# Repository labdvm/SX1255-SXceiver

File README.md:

# SX1255-SXceiver-HAT
This is modified SXceiver by shared schematic from Tatu Peltola.
SX1255 HAT for RPi4-5.
# RPi4/5 with minimum 2GB RAM, fast-write micro-sd card or upgraded with M.2 nvme drive.
# The eeprom is for HW-ID and if cannot be programmed by the procedures then you must programm with eeprom programmator. " https://github.com/tejeez/sxxcvr/blob/main/dts/README.md ".
# For Tetra-TMO Base Station this is the installing procedures, " https://github.com/MidnightBlueLabs/tetra-bluestation-docs/wiki ".
https://github.com/MidnightBlueLabs/tetra-bluestation

# The PA (TQP3M9036) can amplify up to 20dBm @ (70cm-band) 
# BlueStation Tetra TMO configurator " https://dimetra.russel053.com/ "
# Z32IT

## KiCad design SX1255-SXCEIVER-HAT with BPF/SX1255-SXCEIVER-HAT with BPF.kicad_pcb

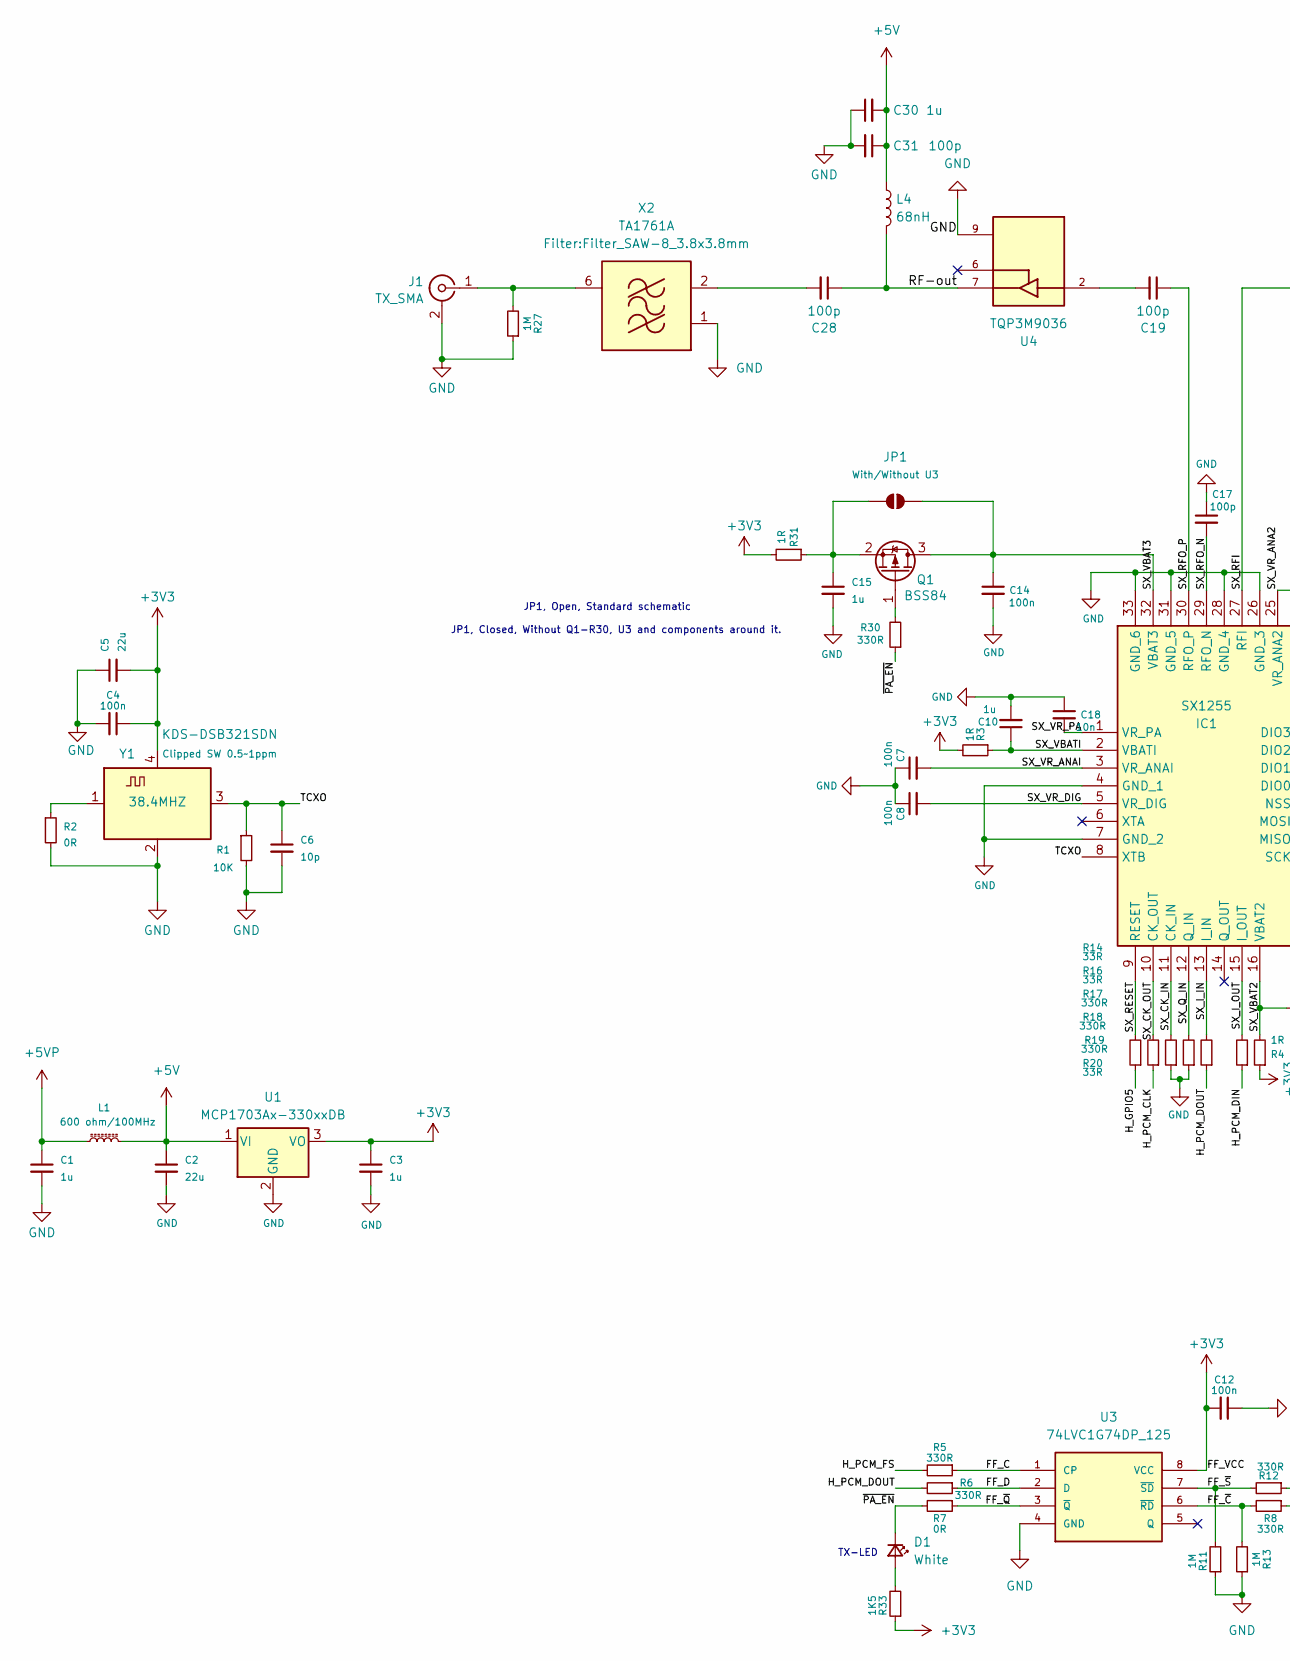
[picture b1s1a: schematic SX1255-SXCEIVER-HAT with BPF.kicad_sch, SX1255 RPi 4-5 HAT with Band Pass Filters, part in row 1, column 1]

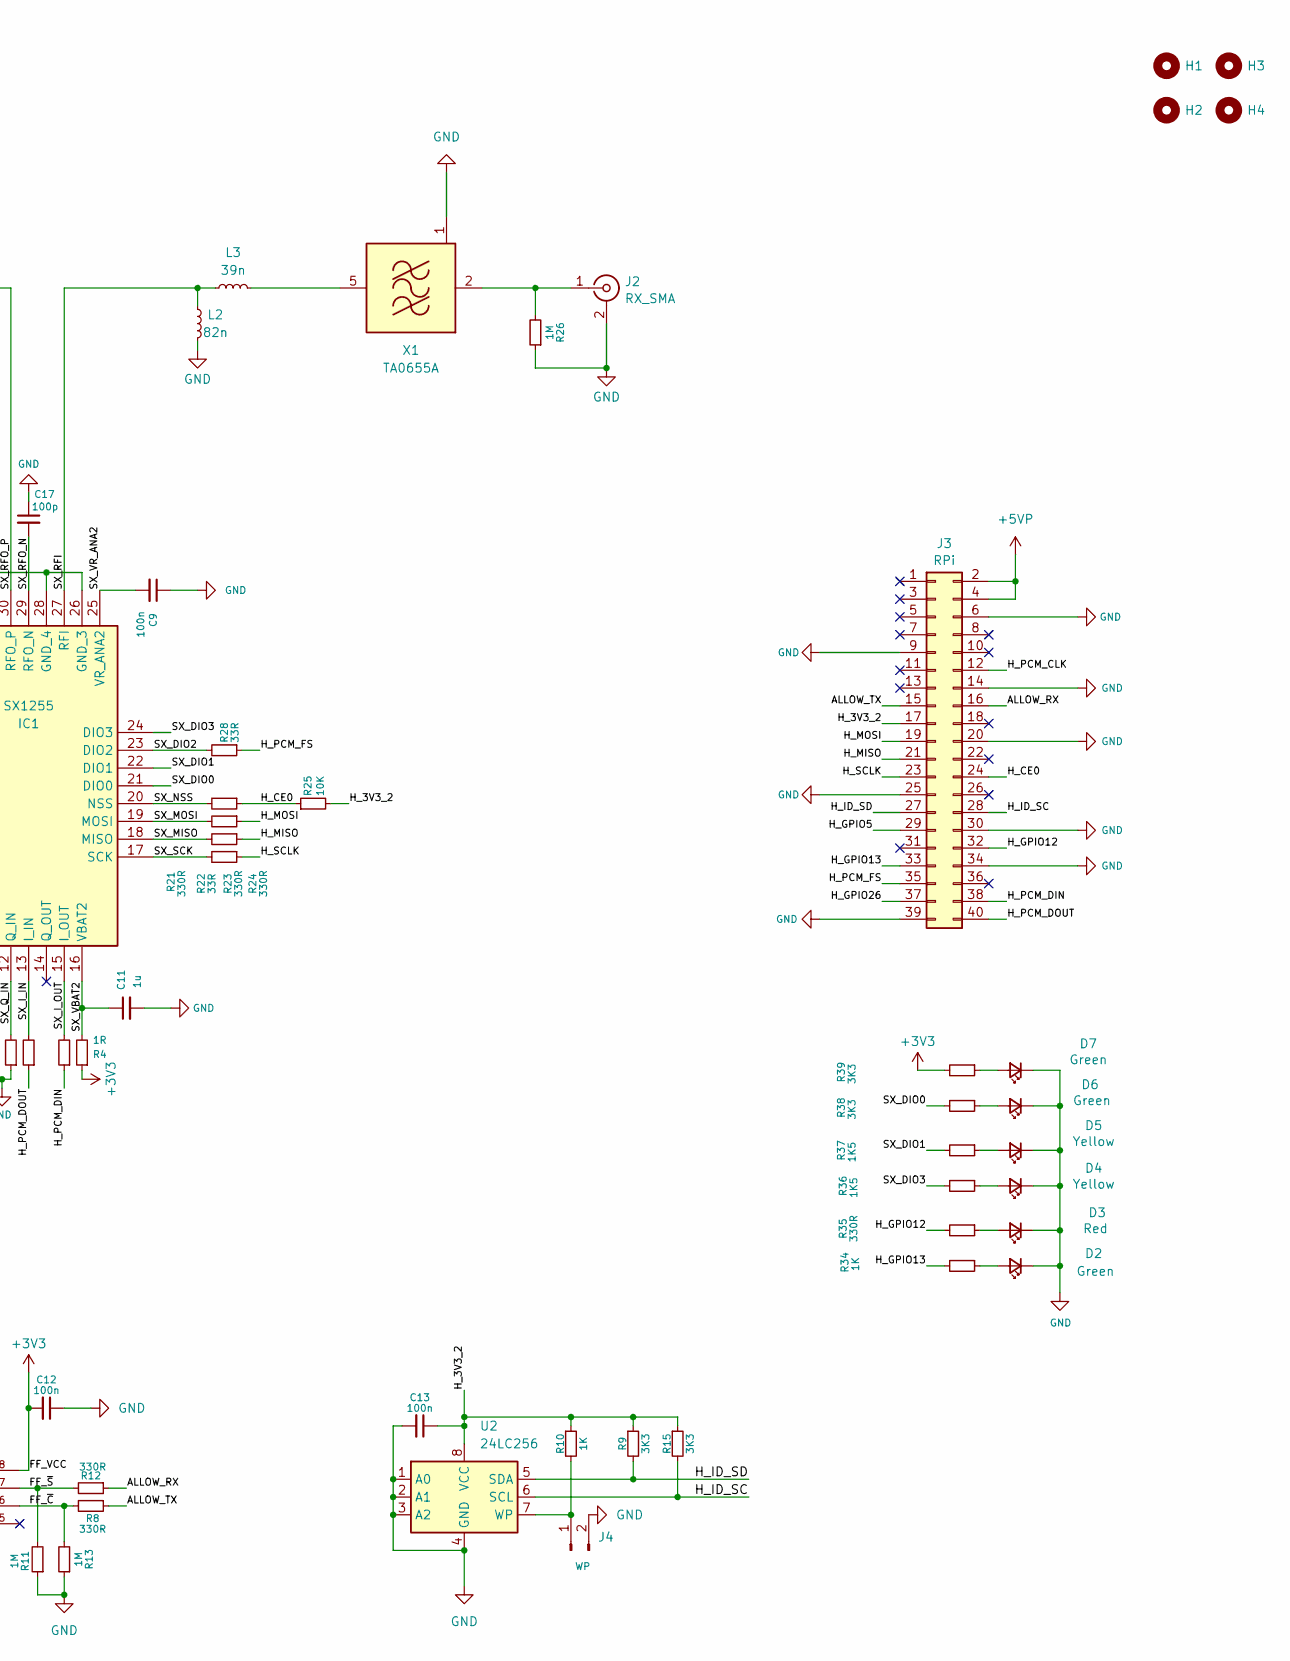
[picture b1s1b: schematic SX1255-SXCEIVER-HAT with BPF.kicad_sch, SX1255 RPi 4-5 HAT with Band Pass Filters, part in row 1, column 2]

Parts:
C1, C3, C10, C11, C15, C30: 1u; C_0603_1608Metric
C2, C5: 22u; C_1206_3216Metric
C4, C7, C8, C9, C12, C13, C14: 100n; C_0603_1608Metric
C6: 10p; C_0603_1608Metric
C17, C19, C28, C31: 100p; C_0603_1608Metric
C18: 10n; C_0603_1608Metric
D1: White; LED_0603_1608Metric_Pad1.05x0.95mm_HandSolder
D2, D6, D7: Green; LED_0603_1608Metric_Pad1.05x0.95mm_HandSolder
D3: Red; LED_0603_1608Metric_Pad1.05x0.95mm_HandSolder
D4, D5: Yellow; LED_0603_1608Metric_Pad1.05x0.95mm_HandSolder
H1, H2, H3, H4: MountingHole; MountingHole_2.7mm_M2.5_DIN965
IC1: SX1255; QFN50P500X500X80-33N-D; MPN SX1255IWLTRT
J1: TX_SMA; SMA_Amphenol_901-144_Vertical
J2: RX_SMA; SMA_Amphenol_901-144_Vertical
J3: RPi; PinSocket_2x20_P2.54mm_Vertical
J4: WP; PinHeader_1x02_P2.54mm_Vertical
JP1: With/Without U3; SolderJumper-2_P1.3mm_Open_RoundedPad1.0x1.5mm
L1: 600 ohm/100MHz; L_0805_2012Metric
L2: 82n; L_0603_1608Metric
L3: 39n; L_0603_1608Metric
L4: 68nH; C_0603_1608Metric
Q1: BSS84; SOT-23
R1, R25: 10K; R_0603_1608Metric
R2, R7: 0R; R_0603_1608Metric
R3, R4, R31: 1R; R_0603_1608Metric
R5, R6, R8, R12, R17, R18, R19, R21, R23, R24, R30, R35: 330R; R_0603_1608Metric
R9, R15, R38, R39: 3K3; R_0603_1608Metric
R10, R34: 1K; R_0603_1608Metric
R11, R13, R26, R27: 1M; R_0603_1608Metric
R14, R16, R20, R22, R28: 33R; R_0603_1608Metric
R33, R36, R37: 1K5; R_0603_1608Metric
U1: MCP1703Ax-330xxDB; SOT-223-3_TabPin2
U2: 24LC256; SOIC-8_3.9x4.9mm_P1.27mm
U3: 74LVC1G74DP_125; SOP65P400X110-8N; MOUSER_PART_NUMBER 771-LVC1GDP125
U4: TQP3M9036; SON50P200X200X95-9N; PARTREV N/A
X1: TA0655A; Filter_SAW-6_3.8x3.8mm
X2: TA1761A; Filter_SAW-8_3.8x3.8mm
Y1: 38.4MHZ; Crystal_SMD_3225-4Pin_3.2x2.5mm

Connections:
+3V3: C3.1, C4.1, C5.2, C12.2, R3.2, R4.1, R31.2, R33.1, R39.2, U1.3 (VO), U3.8 (VCC), Y1.4 (VDD)
+5V: C2.1, C30.2, C31.1, L1.2, L4.1, U1.1 (VI)
+5VP: C1.1, J3.2, J3.4, L1.1
/ALLOW_RX: J3.16, R12.1
/ALLOW_TX: J3.15, R8.1
/FF_C: R5.1, U3.1 (CP)
/FF_D: R6.1, U3.2 (D)
/FF_~C: R8.2, R13.2, U3.6 (~RD)
/FF_~Q: R7.1, U3.3 (~Q)
/FF_~S: R11.2, R12.2, U3.7 (~SD)
/H_3V3_2: C13.1, J3.17, R9.1, R10.1, R15.1, R25.2, U2.8 (VCC)
/H_CE0: J3.24, R24.1, R25.1
/H_GPIO5: J3.29, R14.1
/H_GPIO12: J3.32, R35.2
/H_GPIO13: J3.33, R34.2
/H_GPIO26: J3.37
/H_ID_SC: J3.28, R15.2, U2.6 (SCL)
/H_ID_SD: J3.27, R9.2, U2.5 (SDA)
/H_MISO: J3.21, R22.1
/H_MOSI: J3.19, R23.1
/H_PCM_CLK: J3.12, R16.1
/H_PCM_DIN: J3.38, R20.1
/H_PCM_DOUT: J3.40, R6.2, R19.1
/H_PCM_FS: J3.35, R5.2, R28.1
/H_SCLK: J3.23, R21.1
/RF-out: C28.1, L4.2, U4.7
/SX_CK_IN: IC1.11 (CK_IN), R17.2
/SX_CK_OUT: IC1.10 (CK_OUT), R16.2
/SX_DIO0: IC1.21 (DIO0), R38.2
/SX_DIO1: IC1.22 (DIO1), R37.2
/SX_DIO2: IC1.23 (DIO2), R28.2
/SX_DIO3: IC1.24 (DIO3), R36.2
/SX_I_IN: IC1.13 (I_IN), R19.2
/SX_I_OUT: IC1.15 (I_OUT), R20.2
/SX_MISO: IC1.18 (MISO), R22.2
/SX_MOSI: IC1.19 (MOSI), R23.2
/SX_NSS: IC1.20 (NSS), R24.2
/SX_Q_IN: IC1.12 (Q_IN), R18.2
/SX_RESET: IC1.9 (RESET), R14.2
/SX_RFI: IC1.27 (RFI), L2.2, L3.2
/SX_RFO_N: C17.2, IC1.29 (RFO_N)
/SX_RFO_P: C19.1, IC1.30 (RFO_P)
/SX_SCK: IC1.17 (SCK), R21.2
/SX_VBAT2: C11.1, IC1.16 (VBAT2), R4.2
/SX_VBAT3: C14.1, IC1.32 (VBAT3), JP1.2 (B), Q1.3 (D)
/SX_VBATI: C10.1, IC1.2 (VBATI), R3.1
/SX_VR_ANA2: C9.2, IC1.25 (VR_ANA2)
/SX_VR_ANAI: C7.2, IC1.3 (VR_ANAI)
/SX_VR_DIG: C8.2, IC1.5 (VR_DIG)
/SX_VR_PA: C18.2, IC1.1 (VR_PA)
/TCXO: C6.1, IC1.8 (XTB), R1.1, Y1.3 (OUT)
/~PA_EN: D1.1 (K), R7.2, R30.1
GND: C1.2, C2.2, C3.2, C4.2, C5.1, C6.2, C7.1, C8.1, C9.1, C10.2, C11.2, C12.1, C13.2, C14.2, C15.2, C17.1, C18.1, C30.1, C31.2, D2.1 (K), D3.1 (K), D4.1 (K), D5.1 (K), D6.1 (K), D7.1 (K), IC1.4 (GND_1), IC1.7 (GND_2), IC1.26 (GND_3), IC1.28 (GND_4), IC1.31 (GND_5), IC1.33 (GND_6), J1.2 (Ext), J2.2 (Ext), J3.6, J3.9, J3.14, J3.20, J3.25, J3.30, J3.34, J3.39, J4.2, L2.1, R1.2, R2.2, R11.1, R13.1, R17.1, R18.1, R26.1, R27.1, U1.2 (GND), U2.1 (A0), U2.2 (A1), U2.3 (A2), U2.4 (GND), U3.4 (GND), U4.1, U4.3, U4.4, U4.5, U4.8, U4.9, U4.V1, U4.V2, U4.V3, X1.1 (GND), X1.3 (GND), X1.4 (GND), X1.6 (GND), X2.1 (GND), X2.3 (GND), X2.4 (GND), X2.5 (GND), X2.7 (GND), X2.8 (GND), Y1.2 (GND)
unnamed: C19.2, U4.2
unnamed: D1.2 (A), R33.2
unnamed: D2.2 (A), R34.1
unnamed: D3.2 (A), R35.1
unnamed: D4.2 (A), R36.1
unnamed: D5.2 (A), R37.1
unnamed: D6.2 (A), R38.1
unnamed: D7.2 (A), R39.1
unnamed: J1.1 (In), R27.2, X2.6 (RF_out)
unnamed: J2.1 (In), R26.2, X1.2 (IN)
unnamed: J4.1, R10.2, U2.7 (WP)
unnamed: C15.1, JP1.1 (A), Q1.2 (S), R31.1
unnamed: Q1.1 (G), R30.2
unnamed: L3.1, X1.5 (OUT)
unnamed: C28.2, X2.2 (RF_In)
unnamed: R2.1, Y1.1 (Tri-State)

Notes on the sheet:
JP1, Open, Standard schematic
TX-LED
JP1, Closed, Without Q1-R30, U3 and components around it.

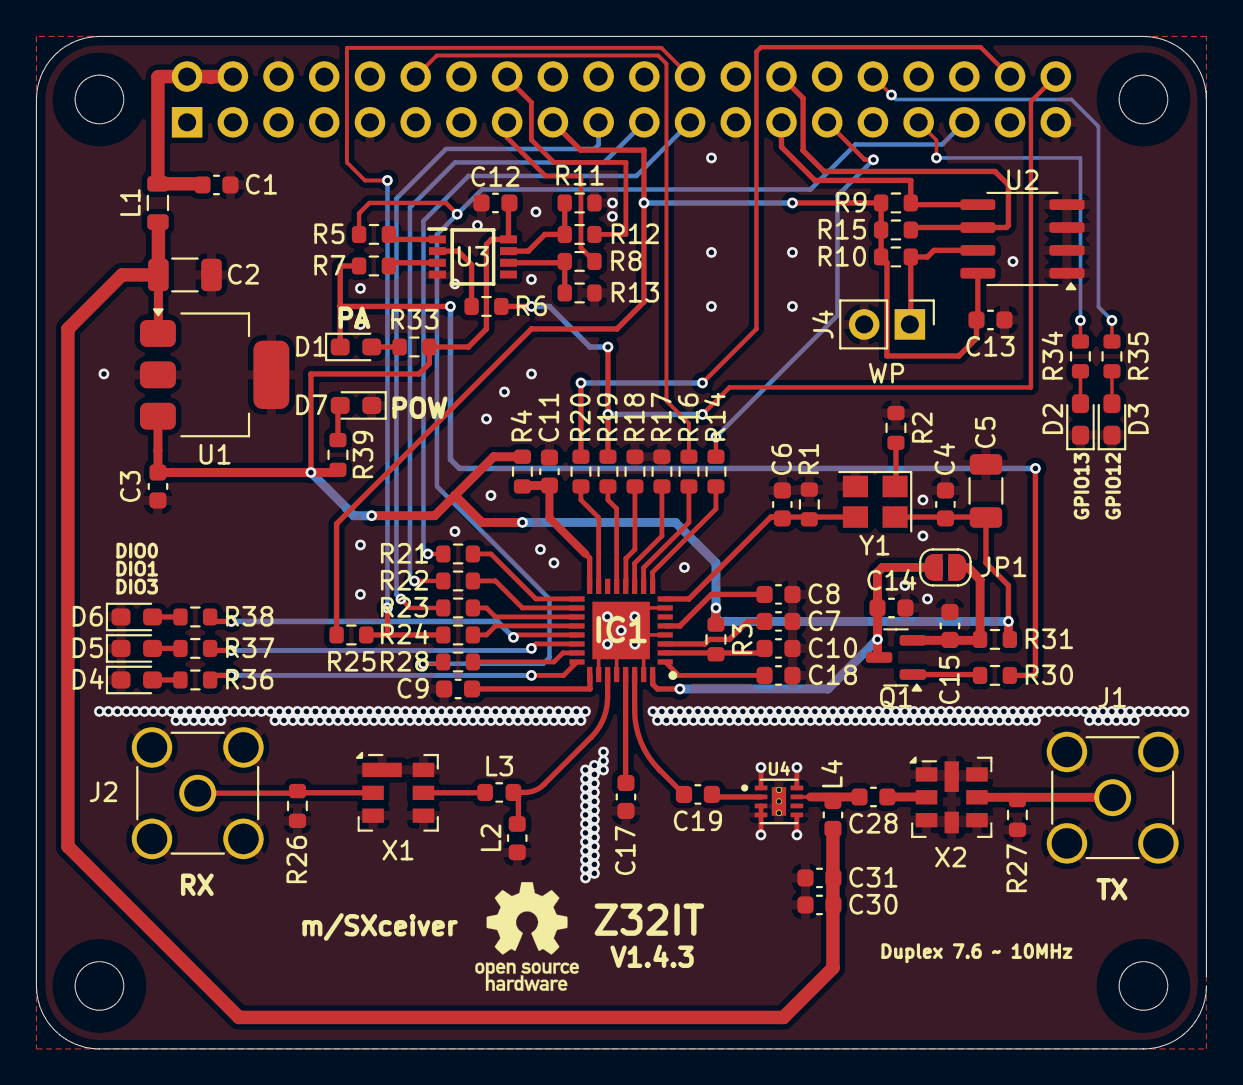
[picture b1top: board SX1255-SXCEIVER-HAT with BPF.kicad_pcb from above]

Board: 2 copper layers, 65.0 x 56.2 mm, 87 parts (1 on the bottom side), 68 nets.

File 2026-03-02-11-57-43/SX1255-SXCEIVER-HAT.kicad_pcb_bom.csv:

Designator,Quantity,Value,Footprint,Package,MPN,DNP,Mount_Type,Description,Sim.Pin,Height,PN,PROD_ID,MANUFACTURER_NAME,MF,MOUSER_PRICE-STOCK,DESCRIPTION,MOUSER_PART_NUMBER,Price,Check_prices,HEIGHT,SnapEDA_Link,MP,Description_1,Availability,MANUFACTURER_PART_NUMBER,MAXIMUM_PACKAGE_HEIGHT,STANDARD,PARTREV,Purchase-URL,MANUFACTURER
"C1, C10, C11, C15, C3, C30",6,1u,C_0603_1608Metric,,,,smt,,,,,,,,,,,,,,,,,,,,,,,
"C12, C13, C14, C4, C7, C8, C9",7,100n,C_0603_1608Metric,,,,smt,,,,,,,,,,,,,,,,,,,,,,,
"C17, C19, C28, C31",4,100p,C_0603_1608Metric,,,,smt,,,,,,,,,,,,,,,,,,,,,,,
C18,1,10n,C_0603_1608Metric,,,,smt,,,,,,,,,,,,,,,,,,,,,,,
"C2, C5",2,22u,C_1206_3216Metric,,,,smt,,,,,,,,,,,,,,,,,,,,,,,
C6,1,10p,C_0603_1608Metric,,,,smt,,,,,,,,,,,,,,,,,,,,,,,
D1,1,White,LED_0603_1608Metric_Pad1.05x0.95mm_HandSolder,,,,smt,"Light emitting diode, small symbol",1=K 2=A,,,,,,,,,,,,,,,,,,,,,
"D4, D5",2,Yellow,LED_0603_1608Metric_Pad1.05x0.95mm_HandSolder,,,,smt,"Light emitting diode, small symbol",1=K 2=A,,,,,,,,,,,,,,,,,,,,,
"D6, D7",2,Green,LED_0603_1608Metric_Pad1.05x0.95mm_HandSolder,,,,smt,"Light emitting diode, small symbol",1=K 2=A,,,,,,,,,,,,,,,,,,,,,
F1,1,6V/0.5A,Fuse_1206_3216Metric,,,,smt,"Resettable fuse, polymeric positive temperature coefficient, small symbol",,,,,,,,,,,,,,,,,,,,,,
"FL1, FL2",2,LFCN-490,Filter_Mini-Circuits_FV1206,,,,smt,"490MHz 50 Ohm Passive Low Pass Filter, FV1206",,,,,,,,,,,,,,,,,,,,,,
IC1,1,SX1255,QFN50P500X500X80-33N-D,,SX1255IWLTRT,,smt,,,0.8,947-SX1255IWLTRT,,,,,,,,,,,,,,,,,,,
"J1, J2",2,U.FL,U.FL,,,,smt,SMA PCB Edge Mount connector SMD,,,,CONN-09193,,,,,,,,,,,,,,,,,,
L1,1,600 ohm/100MHz,L_0603_1608Metric,,,,smt,"Inductor with ferrite core, small symbol",,,,,,,,,,,,,,,,,,,,,,
L2,1,82n,L_0603_1608Metric,,,,smt,,,,,,,,,,,,,,,,,,,,,,,
L3,1,39n,L_0603_1608Metric,,,,smt,,,,,,,,,,,,,,,,,,,,,,,
L4,1,68nH,C_0603_1608Metric,,,,smt,Inductor,,,,,,,,,,,,,,,,,,,,,,
Q1,1,BSS84,SOT-23,,,,smt,"-0.13A Id, -50V Vds, P-Channel MOSFET, SOT-23",,,,,,,,,,,,,,,,,,,,,,
"R1, R25",2,10K,R_0603_1608Metric,,,,smt,,,,,,,,,,,,,,,,,,,,,,,
R10,1,1K,R_0603_1608Metric,,,,smt,,,,,,,,,,,,,,,,,,,,,,,
"R11, R13, R26, R27",4,1M,R_0603_1608Metric,,,,smt,,,,,,,,,,,,,,,,,,,,,,,
"R12, R17, R18, R19, R21, R23, R24, R30, R5, R6, R8",11,330R,R_0603_1608Metric,,,,smt,,,,,,,,,,,,,,,,,,,,,,,
"R14, R16, R20, R22, R28",5,33R,R_0603_1608Metric,,,,smt,,,,,,,,,,,,,,,,,,,,,,,
"R15, R38, R39, R9",4,3K3,R_0603_1608Metric,,,,smt,,,,,,,,,,,,,,,,,,,,,,,
"R2, R7",2,0R,R_0603_1608Metric,,,,smt,opt.,,,,,,,,,,,,,,,,,,,,,,
"R3, R31, R4",3,1R,R_0603_1608Metric,,,,smt,,,,,,,,,,,,,,,,,,,,,,,
"R33, R36, R37",3,1K5,R_0603_1608Metric,,,,smt,,,,,,,,,,,,,,,,,,,,,,,
U1,1,MCP1703Ax-330xxDB,SOT-223-3_TabPin2,,,,smt,"Low Quiescent Current LDO Regulator, 3.3V, 250mA, Vin<=16V, SOT-223",,,,,,,,,,,,,,,,,,,,,,
U2,1,24LC256,SOIC-8_3.9x4.9mm_P1.27mm,,,,smt,"I2C Serial EEPROM, 256Kb, DIP-8/SOIC-8/TSSOP-8/DFN-8",,,,,,,,,,,,,,,,,,,,,,
U3,1,74LVC1G74DP_125,SOP65P400X110-8N,TSSOP8-8 Nexperia USA Inc.,,,smt,,,,,,Nexperia,NXP USA Inc.,https://www.mouser.co.uk/ProductDetail/Nexperia/74LVC1G74DP1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,74LVC1G74 - Single D-type flip-flop with set and reset; positive edge trigger@en-us,771-LVC1GDP125,None,"https://www.snapeda.com/parts/74LVC1G74DP,125/NXP+Semiconductors/view-part/?ref=eda",1.1mm,"https://www.snapeda.com/parts/74LVC1G74DP,125/NXP+Semiconductors/view-part/?ref=snap","74LVC1G74DP,125","Flip Flop 1 Element D-Type 1 Bit Positive Edge 8-TSSOP, 8-MSOP (0.118, 3.00mm Width)",In Stock,"74LVC1G74DP,125",,,,,
U4,1,TQP3M9036,SON50P200X200X95-9N,DFN-8 Qorvo,,,smt,,,,,,,Qorvo,,,,None,https://www.snapeda.com/parts/TQP3M9036/Qorvo/view-part/?ref=eda,,https://www.snapeda.com/parts/TQP3M9036/Qorvo/view-part/?ref=snap,TQP3M9036,RF Amp Chip Single GP 2GHz 5.25V 8-Pin DFN EP T/R,In Stock,,0.95mm,IPC-7351B,N/A,https://www.snapeda.com/api/url_track_click_mouser/?unipart_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,Qorvo
Y1,1,TCXO 38.40MHz,Crystal_SMD_3225-4Pin_3.2x2.5mm,,,,smt,Clipped SW 0.5~1.5ppm,,,,,,,,,,,,,,,,,,,,,,

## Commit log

2026-02-28 Enhance README with project details
    Updated project description with additional details.
2026-02-28 Rename project to SX1255-SXceiver-HAT
2026-02-28 Update README with RPi4-5 recommendations
    Added hardware recommendations for Raspberry Pi.
2026-03-01 Enhance README with setup and configuration details
    Added detailed setup instructions and recommendations for SX1255 HAT.
2026-03-02 Add files via upload
    The BOM file is empty !!!
2026-03-02 Update README with amplifier setup details
    Added additional information about TQP3M9036 amplifier setup.
2026-03-15 Update README to reflect BlueStation in configurator link
2026-03-15 Revise RAM requirements and PA description in README
    Updated RAM recommendation for RPi4/5 and clarified PA description.
2026-03-15 Update README with SX-HAT configuration details
    Added details about the main SX-HAT configurations.
